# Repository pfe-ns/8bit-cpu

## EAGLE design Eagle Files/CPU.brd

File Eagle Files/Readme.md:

## This folder contains Schematics and and Board Layout files that are used to produce this CPU

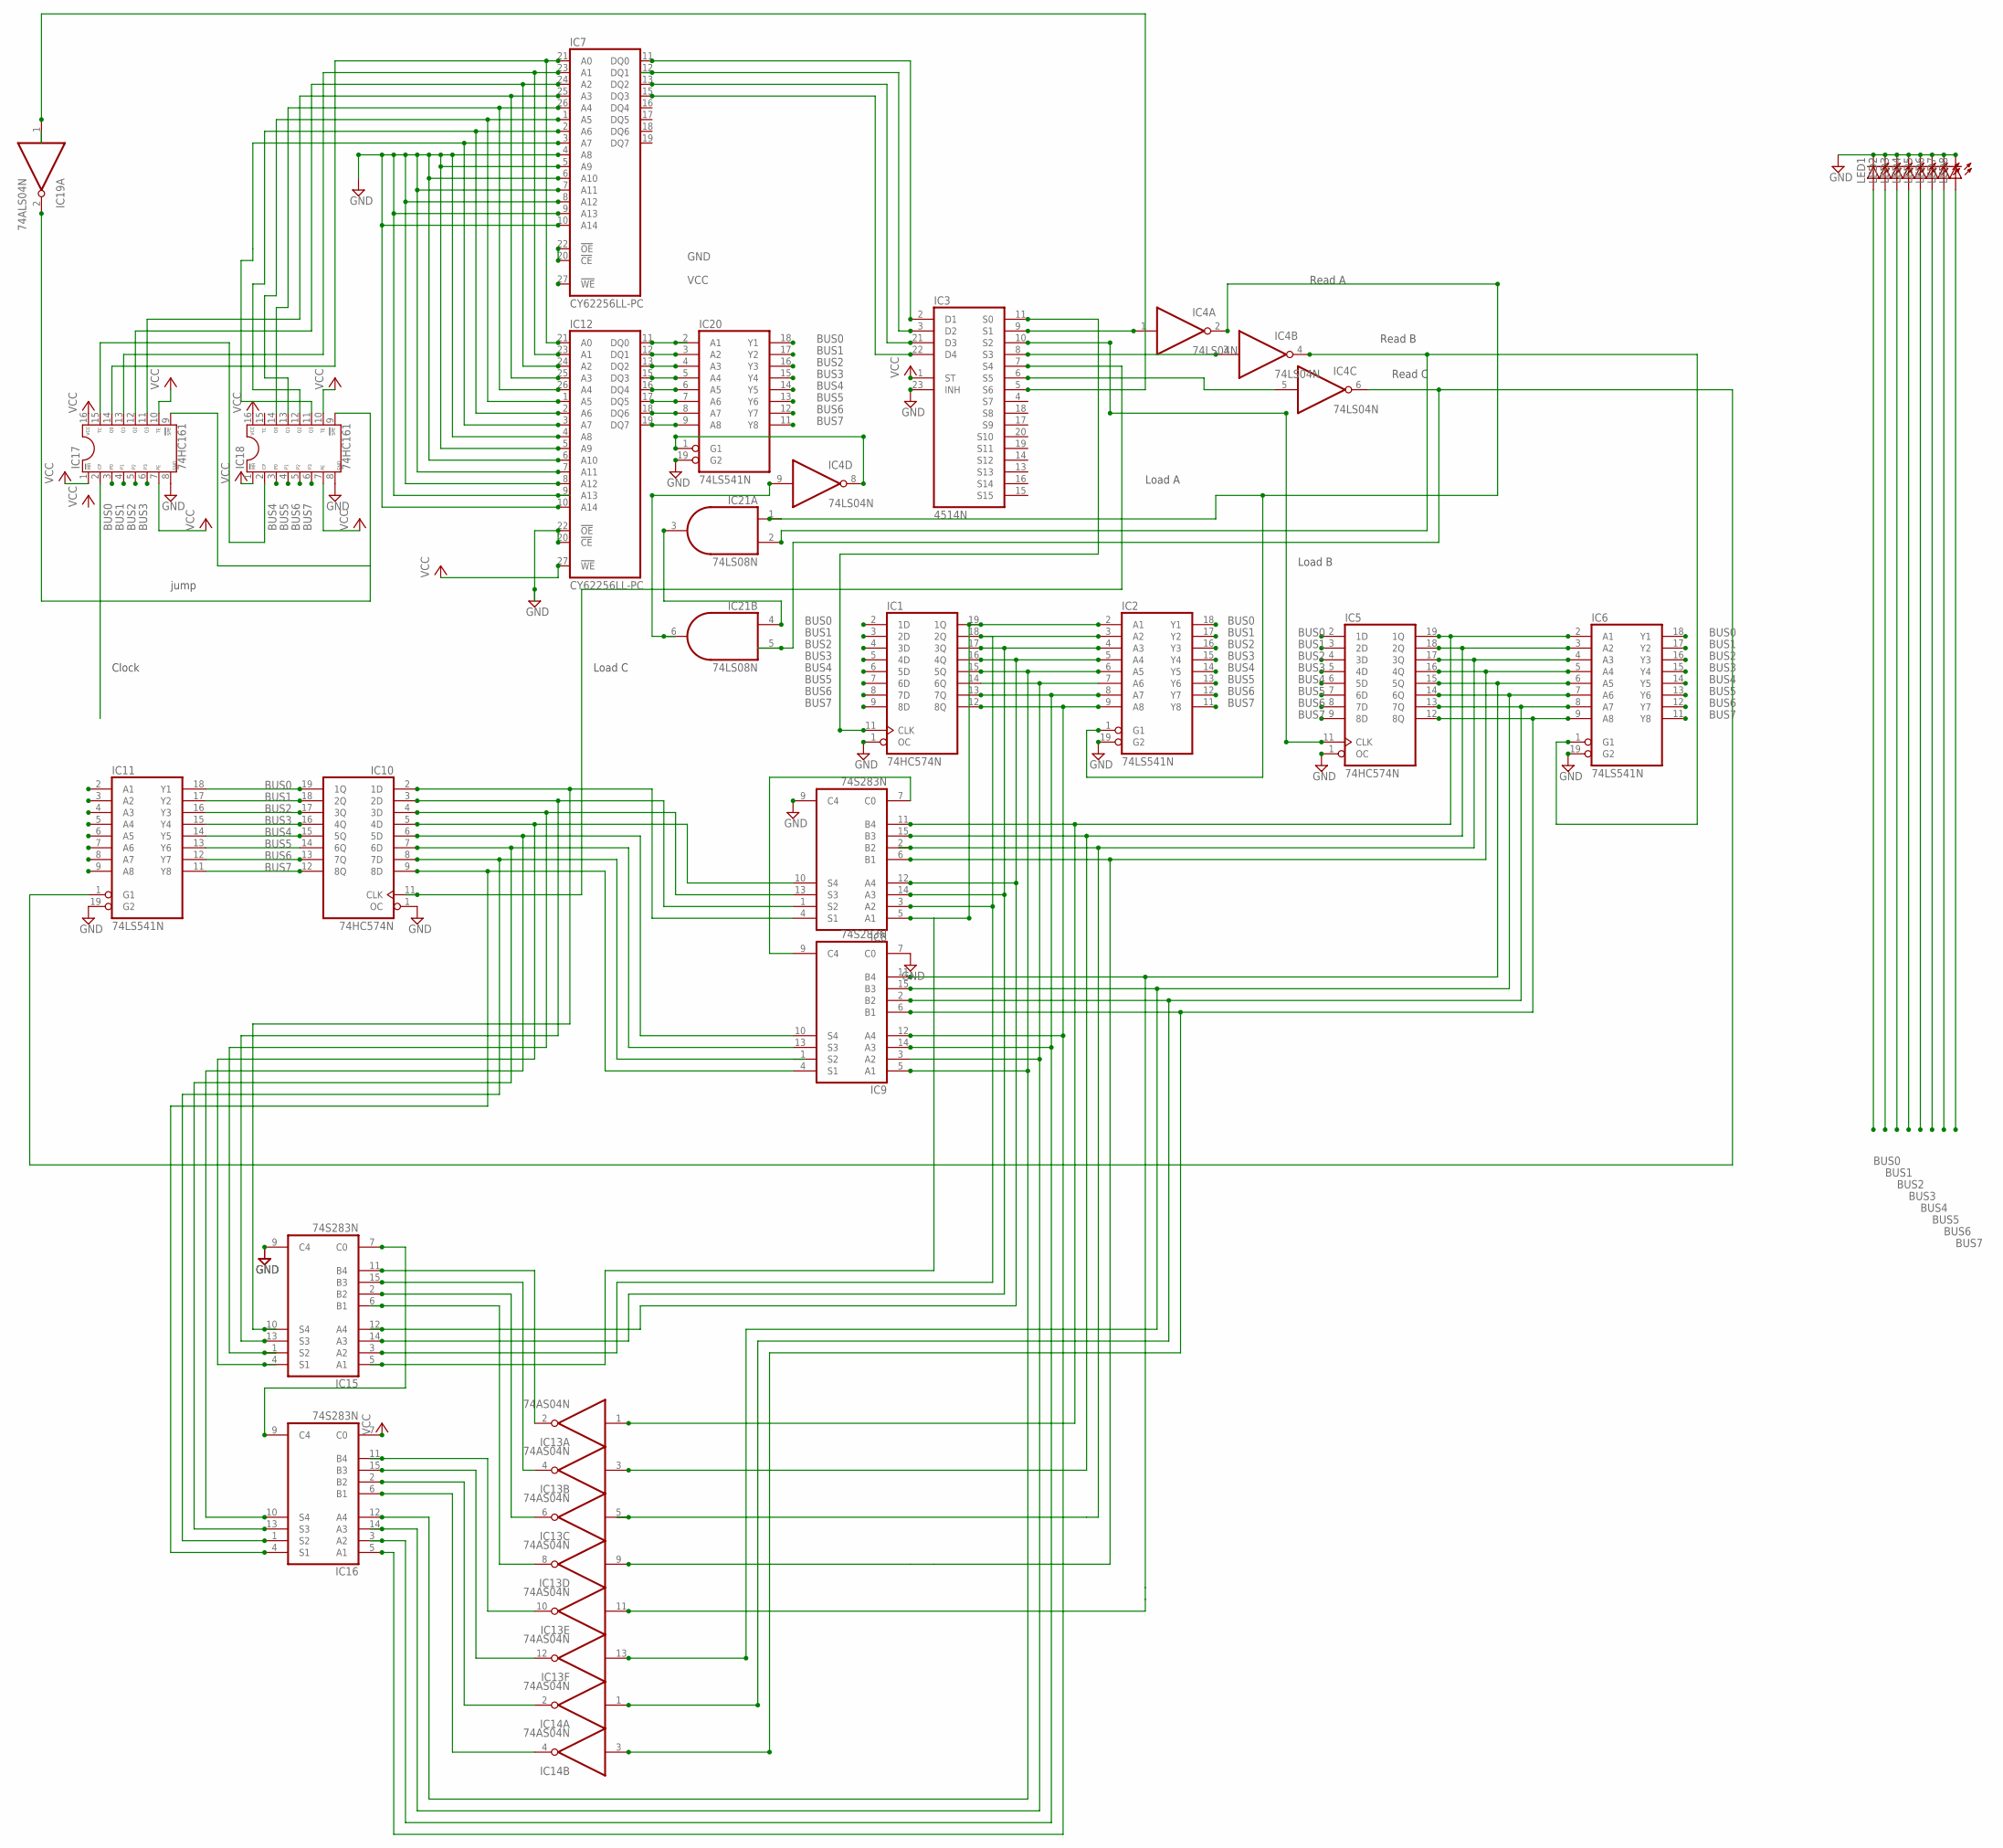
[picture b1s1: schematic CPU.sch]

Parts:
IC1, IC5, IC10: 74HC574N; DIL20
IC2, IC6, IC11, IC20: 74LS541N; DIL20
IC3: 4514N; DIL24-6
IC4: 74LS04N; DIL14
IC7, IC12: CY62256LL-PC; DIL28-6
IC8, IC9, IC15, IC16: 74S283N; DIL16
IC13, IC14: 74AS04N; DIL14
IC17, IC18: DIL16
IC19: 74ALS04N; DIL14
IC21: 74LS08N; DIL14
LED1, LED2, LED3, LED4, LED5, LED6, LED7, LED8: LED_ELD260; LED_LD260

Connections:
BUS0: IC1.2 (1D), IC2.18 (Y1), IC5.2 (1D), IC6.18 (Y1), IC11.2 (A1), IC17.3 (P0), IC20.18 (Y1), LED1.A
BUS1: IC1.3 (2D), IC2.17 (Y2), IC3.10 (S2), IC5.3 (2D), IC5.11 (CLK), IC6.17 (Y2), IC11.3 (A2), IC17.4 (P1), IC20.17 (Y2), LED2.A
BUS2: IC1.4 (3D), IC2.16 (Y3), IC5.4 (3D), IC6.16 (Y3), IC11.4 (A3), IC17.5 (P2), IC20.16 (Y3), LED3.A
BUS3: IC1.5 (4D), IC1.11 (CLK), IC2.15 (Y4), IC3.11 (S0), IC5.5 (4D), IC6.15 (Y4), IC11.5 (A4), IC17.6 (P3), IC20.15 (Y4), LED4.A
BUS4: IC1.6 (5D), IC2.14 (Y5), IC5.6 (5D), IC6.14 (Y5), IC11.6 (A5), IC18.3 (P0), IC20.14 (Y5), LED5.A
BUS5: IC1.7 (6D), IC2.13 (Y6), IC5.7 (6D), IC6.13 (Y6), IC11.7 (A6), IC18.4 (P1), IC20.13 (Y6), LED6.A
BUS6: IC1.8 (7D), IC2.12 (Y7), IC5.8 (7D), IC6.12 (Y7), IC11.8 (A7), IC18.5 (P2), IC20.12 (Y7), LED7.A
BUS7: IC1.9 (8D), IC2.11 (Y8), IC5.9 (8D), IC6.11 (Y8), IC11.9 (A8), IC18.6 (P3), IC20.11 (Y8), LED8.A
GND: IC1.1 (OC), IC1.10 (GND), IC2.10 (GND), IC2.19 (G2), IC3.23 (INH), IC4.7 (GND), IC5.1 (OC), IC5.10 (GND), IC6.10 (GND), IC6.19 (G2), IC7.4 (A8), IC7.5 (A9), IC7.6 (A10), IC7.7 (A11), IC7.8 (A12), IC7.9 (A13), IC7.10 (A14), IC7.14 (GND), IC7.20 (!CE), IC7.22 (!OE), IC8.8 (GND), IC8.9 (C4), IC9.7 (C0), IC9.8 (GND), IC10.1 (OC), IC10.10 (GND), IC11.10 (GND), IC11.19 (G2), IC12.4 (A8), IC12.5 (A9), IC12.6 (A10), IC12.7 (A11), IC12.8 (A12), IC12.9 (A13), IC12.10 (A14), IC12.14 (GND), IC12.20 (!CE), IC12.22 (!OE), IC13.7 (GND), IC14.7 (GND), IC15.8 (GND), IC15.9 (C4), IC16.8 (GND), IC17.8 (GND), IC18.8 (GND), IC19.7 (GND), IC20.10 (GND), IC20.19 (G2), IC21.7 (GND), LED1.K (C), LED2.K (C), LED3.K (C), LED4.K (C), LED5.K (C), LED6.K (C), LED7.K (C), LED8.K (C)
unnamed: IC1.19 (1Q), IC2.2 (A1), IC8.5 (A1), IC15.5 (A1)
unnamed: IC1.18 (2Q), IC2.3 (A2), IC8.3 (A2), IC15.3 (A2)
unnamed: IC1.17 (3Q), IC2.4 (A3), IC8.14 (A3), IC15.14 (A3)
unnamed: IC1.14 (6Q), IC2.7 (A6), IC9.3 (A2), IC16.14 (A3)
unnamed: IC1.15 (5Q), IC2.6 (A5), IC9.5 (A1), IC16.12 (A4)
unnamed: IC4.8 (O), IC20.1 (G1)
unnamed: IC1.13 (7Q), IC2.8 (A7), IC9.14 (A3), IC16.3 (A2)
unnamed: IC1.12 (8Q), IC2.9 (A8), IC9.12 (A4), IC16.5 (A1)
unnamed: IC3.2 (D1), IC7.11 (DQ0)
unnamed: IC3.3 (D2), IC7.12 (DQ1)
unnamed: IC3.21 (D3), IC7.13 (DQ2)
unnamed: IC3.22 (D4), IC7.15 (DQ3)
unnamed: IC3.9 (S1), IC4.1 (I)
unnamed: IC2.1 (G1), IC4.2 (O), IC21.1 (I0)
unnamed: IC13.2 (O), IC15.11 (B4)
unnamed: IC13.4 (O), IC15.15 (B3)
unnamed: IC5.17 (3Q), IC6.4 (A3), IC8.2 (B2)
unnamed: IC5.16 (4Q), IC6.5 (A4), IC8.6 (B1), IC13.9 (I)
unnamed: IC5.15 (5Q), IC6.6 (A5), IC9.11 (B4), IC13.11 (I)
unnamed: IC5.14 (6Q), IC6.7 (A6), IC9.15 (B3), IC13.13 (I)
unnamed: IC5.13 (7Q), IC6.8 (A7), IC9.2 (B2), IC14.1 (I)
unnamed: IC4.4 (O), IC6.1 (G1), IC21.2 (I1)
unnamed: IC3.8 (S3), IC4.3 (I)
unnamed: IC1.16 (4Q), IC2.5 (A4), IC8.12 (A4), IC15.12 (A4)
unnamed: IC8.7 (C0), IC9.9 (C4)
unnamed: IC8.4 (S1), IC10.2 (1D), IC15.10 (S4)
unnamed: IC8.1 (S2), IC10.3 (2D), IC15.13 (S3)
unnamed: IC8.13 (S3), IC10.4 (3D), IC15.1 (S2)
unnamed: IC8.10 (S4), IC10.5 (4D), IC15.4 (S1)
unnamed: IC9.10 (S4), IC10.6 (5D), IC16.10 (S4)
unnamed: IC9.13 (S3), IC10.7 (6D), IC16.13 (S3)
unnamed: IC10.8 (7D), IC16.1 (S2)
unnamed: IC9.4 (S1), IC10.9 (8D), IC16.4 (S1)
unnamed: IC10.19 (1Q), IC11.18 (Y1)
unnamed: IC10.18 (2Q), IC11.17 (Y2)
unnamed: IC10.17 (3Q), IC11.16 (Y3)
unnamed: IC10.16 (4Q), IC11.15 (Y4)
unnamed: IC10.15 (5Q), IC11.14 (Y5)
unnamed: IC10.14 (6Q), IC11.13 (Y6)
unnamed: IC10.13 (7Q), IC11.12 (Y7)
unnamed: IC10.12 (8Q), IC11.11 (Y8)
unnamed: IC3.7 (S4), IC10.11 (CLK)
unnamed: IC3.6 (S5), IC4.5 (I)
unnamed: IC4.6 (O), IC11.1 (G1), IC21.5 (I1)
unnamed: IC7.21 (A0), IC12.21 (A0), IC17.14 (Q0)
unnamed: IC7.23 (A1), IC12.23 (A1), IC17.13 (Q1)
unnamed: IC7.24 (A2), IC12.24 (A2), IC17.12 (Q2)
unnamed: IC7.25 (A3), IC12.25 (A3), IC17.11 (Q3)
unnamed: IC7.26 (A4), IC12.26 (A4), IC18.14 (Q0)
unnamed: IC7.1 (A5), IC12.1 (A5), IC18.13 (Q1)
unnamed: IC7.2 (A6), IC12.2 (A6), IC18.12 (Q2)
unnamed: IC7.3 (A7), IC12.3 (A7), IC18.11 (Q3)
unnamed: IC12.11 (DQ0), IC20.2 (A1)
unnamed: IC12.12 (DQ1), IC20.3 (A2)
unnamed: IC12.13 (DQ2), IC20.4 (A3)
unnamed: IC12.15 (DQ3), IC20.5 (A4)
unnamed: IC12.16 (DQ4), IC20.6 (A5)
unnamed: IC12.17 (DQ5), IC20.7 (A6)
unnamed: IC12.18 (DQ6), IC20.8 (A7)
unnamed: IC5.18 (2Q), IC6.3 (A2), IC8.15 (B3), IC13.3 (I)
unnamed: IC5.19 (1Q), IC6.2 (A1), IC8.11 (B4), IC13.1 (I)
unnamed: IC13.6 (O), IC15.2 (B2)
unnamed: IC13.8 (O), IC15.6 (B1)
unnamed: IC13.10 (O), IC16.11 (B4)
unnamed: IC13.12 (O), IC16.15 (B3)
unnamed: IC5.12 (8Q), IC6.9 (A8), IC9.6 (B1), IC14.3 (I)
unnamed: IC14.2 (O), IC16.2 (B2)
unnamed: IC14.4 (O), IC16.6 (B1)
unnamed: IC17.15 (TC), IC18.2 (CP)
unnamed: IC3.5 (S6), IC19.1 (I)
unnamed: IC17.9 (|SPE), IC18.9 (|SPE), IC19.2 (O)
unnamed: IC15.7 (C0), IC16.9 (C4)
unnamed: IC4.9 (I), IC21.6 (O)
unnamed: IC12.19 (DQ7), IC20.9 (A8)
VCC: IC1.20 (VCC), IC2.20 (VCC), IC3.1 (ST), IC4.14 (VCC), IC5.20 (VCC), IC6.20 (VCC), IC7.27 (!WE), IC7.28 (VCC), IC8.16 (VCC), IC9.16 (VCC), IC10.20 (VCC), IC11.20 (VCC), IC12.27 (!WE), IC12.28 (VCC), IC13.14 (VCC), IC14.14 (VCC), IC15.16 (VCC), IC16.7 (C0), IC16.16 (VCC), IC17.1 (|MR), IC17.7 (PE), IC17.10 (TE), IC17.16 (VCC), IC18.1 (|MR), IC18.7 (PE), IC18.10 (TE), IC18.16 (VCC), IC19.14 (VCC), IC20.20 (VCC), IC21.14 (VCC)
VDD: IC3.24 (VDD)
VSS: IC3.12 (VSS)

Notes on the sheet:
Load A
Read A
Load B
Read B
Load C
Read C
jump
Clock

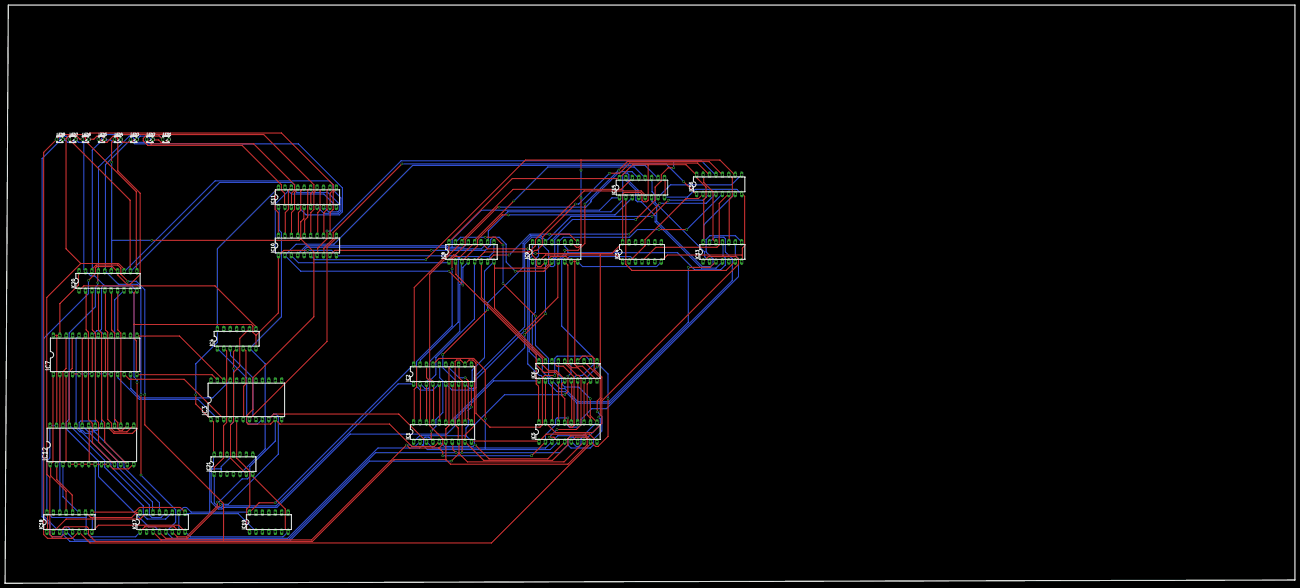
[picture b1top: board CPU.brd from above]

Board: 2 copper layers, 509.2 x 228.3 mm, 29 parts (0 on the bottom side), 84 nets.

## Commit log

2016-09-24 1-bit ALU ver 1.0
    Prva verzija ALU za procesor
2016-09-28 ALU VHDL file
2016-09-28 ALU.txt removed
2016-09-30 Documents file
2016-09-30 ALU update
2016-10-08 ALU update and Control Unit
    Added and , or ,xor , inverter , shift left and shift right to ALU and
    added new module - Control_Unit
2016-10-13 Added RAM , expanded Control Unit
2016-10-14 ALU and Control Unit update
2016-10-14 Added TODO in DOCS
2016-10-19 Added Internal Registers
2016-10-27 Added Program Counter
2016-11-03 Combined all modules to CPU.vhd
2016-11-17 Added USB_Controller
2016-11-17 Updated ALU
2016-11-17 Organised Project in folders
2016-11-17 Simulation working
2017-01-25 Shift right fixed
2017-01-30 PWM module added
2017-01-31 PWM Module working
2017-03-09 Interactive simulator
2017-03-09 Simple instructions added
2017-03-09 Added instruction parser
2017-03-11 jQuery
2017-03-11 Instructions working
2017-03-12 EEPROM_Programmer
2017-03-12 Added write function
2017-03-12 Added Readme
2017-03-12 Added Schematics files
2017-03-13 Added RAM output control
2017-03-13 Updated Schematics
2017-03-13 Removed some bugs with analog pins
2017-03-15 Added Board Layout file
2017-03-15 Rubberduck
2017-03-16 Removed bugs
2017-03-24 Final Schematics
2017-05-08 Added Pull-Up and Pull-Down resistors
2017-05-08 Removed some files
2017-05-08 Bugs removed
2017-05-11 Removed some bugs
2017-06-29 Ready for routing
